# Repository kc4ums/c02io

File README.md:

# C02IO: Raspberry Pi CM5 industrial I/O board (design spec)

**Rev B (2026-11-23): the controller is now a Raspberry Pi Compute Module 5.** Rev A's W65C02S system (CPU, RAM, flash, VIA, UART, address decoding, clock, reset, USB-serial and bus expansion headers) is gone. All the I/O is unchanged except where it meets the logic side, which now runs at 3.3 V. The CM5 adds gigabit Ethernet and a USB-C port for flashing.

Status:
- **Netlist:** `python check_board.py` passes. Every new part was checked against its datasheet (listed at the top of `board.py`).
- **Placement:** `python check_place.py png` passes (no courtyard overlaps, every part inside its isolated area, bridge pads on the right side of each gap). The board grew 10 mm to 230 x 157 mm to fit the 55 x 40 mm module.
- **Schematic:** `python check_sch.py` passes. ERC shows 0 errors and 0 warnings, and KiCad's netlist matches `board.py` (365 nets, 494 parts).
- **PCB:** `mk_pcb.py` builds it. DRC shows 0 errors, with 499 connections still to route.
- **Next:** route it (`python mk_fab.py --route`, see Routing). Lay out the Ethernet and USB pairs carefully first (see Still to do).

This is a small PLC-style controller:
- 16 opto-isolated 24 V digital inputs
- 16 opto-isolated 24 V sourcing outputs, 0.5 A each
- 8 analog inputs and 8 analog outputs, each set to 0-10 V or 4-20 mA with a jumper, isolated as a group
- isolated RS-485 (Modbus RTU)
- gigabit Ethernet, and USB-C for flashing the CM5's eMMC (rpiboot) or a gadget console

## Choices made

| | Choice | Why |
|---|---|---|
| Controller (rev B) | **Raspberry Pi CM5**, on two Amphenol 10164227-1001A1RLF connectors (1.5 mm stack) | Linux, Ethernet, plenty of speed. The footprint is Raspberry Pi's own, from the CM5 IO board's KiCad files (`vendor/cm5io`). Any CM5 variant fits; a Lite one has nowhere to boot from here, so use an eMMC module. |
| Interfaces (rev B) | **Ethernet RJ45, USB-C** | USB-C is a USB 2.0 device port for rpiboot and console. There is no USB host port, HDMI, SD slot or RTC battery. |
| Build | **SMD, assembled by JLCPCB** | You solder the through-hole parts: terminals, headers, the MagJack and the URB converter. |
| Analog | **0-10 V or 4-20 mA, one jumper per channel** | Analog inputs use a 2-pin jumper, analog outputs a 2x3 header with two shunts. |
| Outputs | **Sourcing (high-side), 0.5 A, short-circuit protected** | The standard for PLCs driving relays, valves and lamps. |
| Analog isolation | **Yes, as one group** | The analog section has its own isolated 24 V supply and ground, and talks to the CM5 through digital isolators. The channels share that ground with each other. |
| Layers | **4** | Ground planes under everything, which helps the analog section and the Ethernet pairs. |

## Block diagram

```
 FOUR ISOLATED AREAS: logic (GND), field digital (0V_IO), analog (AGND_ISO), RS-485 (GND_485)

 24V IN --fuse--diode--TVS--+-- TPS54560B buck --> +5V --> CM5 (its 3.3 V output = logic +3V3)
                            +-- URB2424YMD-6WR3 isolated DC-DC --> +24VA, AGND_ISO
                                    +24VA --> 78L05 --> +5VA --> REF3040 (4.096 V)

 CM5 --+-- Ethernet --> MagJack;  USB 2.0 --> USB-C (device)
       |                                                      || FIELD DIGITAL (0V_IO)
       +-- SPI0 <-- 74HC165 x2 <-- pull-ups <-- TLP291-4 x4 <--||---- 16 inputs (LED + opto per input)
       +-- SPI0 --> 74HC595 x2 --> R --> LED of TLP291-4 x4 ---||---> VNI4140K x4 --> 16 outputs, LED each
       |              ^ /OE = watchdog /Q (GPIO5 enable, GPIO4 kick) || STATUS (wire-OR) --> opto --> GPIO22
       |                                                      ||  24V_IO IN --> VNI4140K, 78L05 (+5V_IO); --PTC-->
       |                                                      ||                       sensor supply terminals
       +-- UART0 (RTS = DE) --> CA-IS3082WX -------------------||---- RS-485 A/B (GND_485, from B0505XT)
       +-- SPI1 --> ISO7741 + ISO7720 -------------------------|| ANALOG (AGND_ISO)
                                                              ||-- MCP3208 ADC <-- 8 x (divider, 499R mA jumper, PTC, TVS)
                                                              ||-- DAC7568A --> 8 x (LM324 + NPN, V/I jumper) --> AO
```

Each area has its own ground. Only optocouplers, digital isolators, the isolated DC-DC converters and the isolated RS-485 chip cross between them. The 8 analog channels are isolated from the logic, the field I/O and the power input, but not from each other: they share AGND_ISO.

## CM5 GPIO use

| GPIO | Use |
|---|---|
| 11, 10, 9 | SPI0 SCLK, MOSI, MISO: the shift registers |
| 8 | SPI0 CE0: 74HC595 latch (RCLK). It rises at the end of the transfer, so all 16 outputs change at once. |
| 6 | 74HC165 load (`/PL`): pulse low, then clock the inputs in |
| 21, 20, 19 | SPI1 SCLK, MOSI, MISO, to the analog side through the ISO7741 |
| 18, 16 | SPI1 CE0 = ADC `/CS`, CE2 = DAC `/SYNC` (10k pull-ups) |
| 24 | DAC `/LDAC`: updates all 8 outputs at once |
| 14, 15 | UART0 TX, RX: RS-485 |
| 17 | UART0 RTS: RS-485 driver enable. Use Linux's RS-485 mode, set so the pin is high while sending. A 10k pull-down keeps the driver off during boot, when the bootloader logs on GPIO14/15. |
| 5 | Output enable, pulled low. **The outputs stay off until software sets this.** |
| 4 | Watchdog kick (74HC123: if not toggled for ~100 ms, the outputs drop) |
| 12, 13 | RUN and FAULT LEDs |
| 22 | Output fault in (any VNI4140K over-temperature), through an opto; low = fault |
| 23 | Field power present (24V_IO), through an opto; low = present |
| 2, 3, 7, 25, 26, 27 | Expansion header J11 (2x5): 3V3, 5V, SDA (2), GND, SCL (3), 25, 26, 27, GND, 7. GPIO2/3 have 1.8k pull-ups on the module. |

**One SPI0 transfer does all the digital I/O.** Pulse GPIO6 low, then do one 16-bit transfer on CE0:
- **Out:** the bytes for outputs 16..9 then 8..1, MSB first.
- **In:** the bytes for inputs 8..1 then 16..9, MSB first, low = on. Software inverts them.

CE0 rising at the end of the transfer latches the outputs. Don't use CE0 for a read-only transfer, because it would latch whatever MOSI shifted in.

**Other CM5 pins:**
- **Power and ground:** all 51 ground pins go to GND. 5 V goes to the six VIN pins. GPIO_VREF is tied to the module's own 3.3 V output, which also powers the whole logic side (600 mA max; about 150 mA used).
- **Front-panel controls:** `nRPIBOOT` goes to jumper JP1; fit it before power-up to flash the eMMC over USB-C. `PWR_Button` goes to SW1. The activity LED (`LED_nACT`) is D8.
- **Left open:** PMIC_Enable, EEPROM_nWP, the Wi-Fi/Bluetooth disables, USB_OTG_ID (so it is a device), CC1/CC2, VBAT, fan, SD, PCIe, MIPI, HDMI and USB 3.
- **Power warning:** the CM5 warns about its supply unless it negotiated 5 A over USB-C. Set `PSU_MAX_CURRENT=5000` in its bootloader EEPROM.

## Circuits

**Digital input (x16), IEC 61131-2 type 1/3 style:**
- **Signal path:** terminal → 4.7k (1206) → green LED → opto LED, with 2.2k and 10 nF across the opto LED, then → 0V_IO. An antiparallel 1N4148W protects against reverse voltage.
- **Thresholds:** about 1.7 mA at 11 V reads ON. 5 V stays OFF, because the shunt keeps the opto LED below its threshold. 30 V draws 5.7 mA.
- **Logic side:** the opto transistor pulls the input low against a 22k pull-up to 3.3 V, and a 74HC165 reads it. Software inverts the reading, so 1 = ON.
- **Wiring:** sourcing (PNP) sensors connect between 24V_IO and the input. 0V_IO is the common.

**Digital output (x16):**
- **Signal path:** 74HC595 → 330 Ω → opto LED (about 5 mA from 3.3 V). The opto transistor drives the VNI4140K input from +5V_IO, with a 10k pull-down.
- **Driver:** the VNI4140K is a quad high-side switch: 3.3 V CMOS inputs, 0.6 A per channel in the current datasheet (0.7 A in older ones), current limiting and per-channel thermal shutdown.
- **Indication:** a yellow LED and 4.7k from each output to 0V_IO light when the output is on.
- **Faults:** each VNI4140K has one open-drain STAT pin per channel. All 16 are wire-ORed through one opto to GPIO22. STAT goes low **only on over-temperature** (with IN high), not while the output is current-limiting a short.
- **Supply:** the VNI4140K's exposed slug is **Vcc** (24V_IO), not ground. 24V_IO feeds the four drivers directly (up to 8 A with all outputs on), so **fuse the field supply outside the board**. A reversed field supply is shorted by the SMBJ33A, which must blow that fuse.
- **Start-up and crashes:** the 74HC595s' `/OE` comes from the 74HC123's `/Q`:
  - It stays high (outputs off) until software has written the latches, set GPIO5 and started kicking GPIO4.
  - It goes high again if the kicks stop for about 100 ms. That is about 106 ms at 3.3 V; kick it at least every 25 ms.

**Analog isolation:**
- **Power:** a Mornsun URB2424YMD-6WR3 (9-36 V in, isolated 24 V out, 6 W) makes +24VA on AGND_ISO. A 78L05 makes +5VA for the ADC, DAC and isolators' analog side, and a REF3040 makes the 4.096 V ADC reference.
- **Budget:** 8 outputs at 20 mA from 24 V is about 4 W, plus about 0.5 W for the rest, so the 6 W converter runs at about 75 %.
- **SPI:** an ISO7741 (3 channels to the analog side, 1 back) carries SCLK, MOSI, ADC `/CS` and MISO. An ISO7720 (2 channels) carries DAC `/SYNC` and `/LDAC`. Use the default-high versions, so the chip selects sit inactive while the logic side is unpowered. Side 1 runs at 3.3 V and side 2 at 5 V; the supplies can be set independently. Keep SPI1 at a few MHz: the isolators add about 10 ns each way.

**Analog input (x8):**
- **Signal path:** terminal → PTC (50 mA hold) → SMAJ12A TVS to AGND_ISO → 15k/10k divider (10 V → 4.0 V) → 1k → ADC, with 100 nF and BAV99 clamps to +5VA/AGND_ISO.
- **4-20 mA:** a jumper puts **499 Ω (2010, 0.5 W)** across the input, so 20 mA reads about 9.8 V. Software calibrates it, and a table in software says which channels are mA.
- **ADC:** MCP3208, 12-bit, with a 4.096 V reference (REF3040), so the input range is 0-10.24 V.
- **Mistakes:** 24 V on an input trips the PTC into the TVS.

**Analog output (x8):**
- **DAC:** DAC7568**A**, 12-bit, 8 channels, internal 2.5 V reference, gain 1, so 0-2.5 V. The internal reference is **off at power-up and after a reset**: firmware must enable it. Its outputs drive an LM324 (2 chips, on +24VA), and the op-amp drives an NPN emitter follower (BCX56, SOT-89) from +24VA.
- **Current limit:** a 22 Ω resistor with a sensing transistor limits the output to about 26-29 mA.
- **2x3 jumper:** both shunts left = **0-10 V**: feedback from a 30k/10k divider on the terminal side of the PTC (gain 4), and COM tied to AGND_ISO. Both shunts right = **4-20 mA**: feedback from COM, which returns through a 124 Ω (0.1 %) sense resistor, so 2.5 V gives 20.2 mA.
- **Compensation:** 10k in series with the op-amp's inverting input and 10 nF from its output to that input, plus 10 nF on OUT. These are starting values to check in simulation.
- **Compliance:** about 900 Ω at 20 mA, from the isolated 24 V (only 2.5 V is lost in the sense resistor).
- **Protection:** a PTC and an SMAJ15A TVS at each terminal.
- **Wiring:** in mA mode the load goes between OUT and COM. In V mode, COM is 0 V (AGND_ISO).

**Power:**
- **Input:** 24 V nominal (18-32 V) → 3 A fuse → SS54 reverse diode → SMBJ33A TVS.
- **5 V regulator:** a TPS54560B (4.5-60 V in, 5 A, HSOIC-8) makes +5 V for the CM5 and the RS-485 converter. The values come from TI's 5 V / 5 A design: 400 kHz, B560C catch diode, 10 µH (Bourns SRP1245A), 3 x 47 µF. The CM5 datasheet asks for up to 2.5 A for the module.
- **3.3 V:** from the CM5's own output, so nothing drives a CM5 pin while the module is off.
- **Analog supply:** its own isolated converter (see Analog isolation).
- **Field supply:** 24V_IO is a separate pair of terminals. It can come from the same supply, but isolation only helps if it doesn't.

**RS-485:**
- **Chips:** CA-IS3082WX (isolated transceiver, SOIC-16 wide; logic side 3.3 V, bus side 5 V), powered on the bus side by a B0505XT-1WR3 (SMD) isolated DC-DC converter. The converter needs a 20 mA minimum load, so a 330 Ω resistor (15 mA) sits across its output.
- **Bus side:** a 120 Ω termination jumper (JP3), 680 Ω bias resistors, and an SM712 TVS on A/B.

## Terminals

Pluggable 3.81 mm blocks along the two long edges (headers on the board, plugs in the BOM):

Phoenix MC 1,5/x-G-3.81 headers go up to 16 pins, so the groups are split:

| Ref | Pins | Order |
|---|---|---|
| J2, J3 | 10 each | IN1-IN8 (IN9-IN16), 24V sensor supply (through a 0.5 A PTC), 0V_IO |
| J4 | 10 | OUT1-OUT8, 24V_IO in, 0V_IO in |
| J5 | 10 | OUT9-OUT16, 0V_IO, 0V_IO (load return) |
| J6 | 12 | AI1, AI2, 0V, AI3, AI4, 0V, ... AI7, AI8, 0V |
| J7 | 8 | OUT1, COM1 ... OUT4, COM4 |
| J8 | 9 | OUT5, COM5 ... OUT8, COM8, 0V |
| J1 | 3 | +24 V, 0 V, PE |
| J9 | 3 | A, B, GND_485 |

## Board

- **Size and layers:** **230 x 157 mm**, **4 layers**. Rev A was 230 x 147; the logic band grew 10 mm for the CM5. The 32 field channels sit at the terminals' 3.81 mm pitch, about 45 mm deep with their optos. Each analog channel needs a cell 11 mm (input) or 12.5 mm (output) wide and about 22 mm deep.
- **Bands, top to bottom:** field digital (terminals on the top edge), logic (the CM5 on the right with the Ethernet jack and USB-C on the right edge; 24 V input and power button on the left edge), then analog (terminals on the bottom edge) with RS-485 in the bottom-right corner. The optos, isolators, DC-DC converters and the RS-485 chip straddle the 3 mm gaps between them.
- **Isolation:** four copper areas (logic, field digital, analog, RS-485), each with its own copper on all 4 layers. A ≥3 mm gap separates them, crossed only under the optos, digital isolators, DC-DC converters and the RS-485 chip.
- **B0505XT orientation:** its output 0V (pin 4) is in the same row as the input pins 1 and 2, so its barrier runs between pins 2 and 4, not between the rows. It is turned 270 degrees with the gap between pins 2 and 4. Pin 8 (NC, "isolated from circuitry") ends up on the logic side: leave it unconnected with plane clearance around it.
- **CM5:** nothing is placed under the module, because the 1.5 mm connectors leave no room. Its four M2.5 holes (2.7 mm, unplated) take spacers that suit the stack height.
- **Mounting:** 4 M3 holes, at the left and right edges of the logic band and in the bottom corners. H1 is plated and on PE, with 1 nF 2 kV from PE to logic 0 V. The others are bare. A DIN-rail mount can clip onto the holes.

## Cost notes

- **The CM5** is the biggest item, bought separately and plugged in. Choose an eMMC version.
- **JLCPCB assembly:** most ICs are *extended* parts, each adding a ~$3 loading fee. Check JLCPCB's library for the VNI4140K, CA-IS3082WX, ISO7741/ISO7720, B0505XT-1WR3 and the two Amphenol CM5 connectors. Missing ones can be bought through JLCPCB's global sourcing or soldered by you; the 0.4 mm connectors are best left to JLCPCB.
- **Analog isolation** adds roughly $15-20 per board: the isolated converter (about $8-10) and the two digital isolators.
- **Hand-soldered by you:** the URB2424YMD-6WR3 (through-hole, 25.4 mm square), the TRJG0926HENL MagJack, and the terminal and pin headers.

## Changes in rev B (2026-11-23): CM5 instead of the W65C02S

| Was (rev A) | Now (rev B) | Why |
|---|---|---|
| W65C02S, RAM, flash, W65C22 VIA, TL16C2552 UART, 74HC00/30/138/32 decode, oscillator, DS1813 | Raspberry Pi CM5 | Your request. |
| 74HC541 input buffers, 74HC574 output latches (on the CPU bus) | 74HC165 / 74HC595 shift registers on SPI0 | The CM5 has no parallel bus. |
| `/OE` = NAND(PB0, watchdog OK) | `/OE` = the 74HC123's `/Q`, with `/R` = GPIO5 | The same behaviour without a gate. |
| 5 V logic, 1k opto LED resistors | 3.3 V logic from the CM5, 330 Ω (TLP291 VF 1.2 V, about 5 mA) | CM5 GPIO is 3.3 V. Every logic-side part is rated for it. |
| RS-485 DE = NOT(`/RTSA`) | DE = GPIO17 (UART0 RTS), 10k pull-down | Linux RS-485 mode drives RTS high while sending. |
| USB-serial header, 2x16 bus expansion header | USB-C (device) and a 2x5 GPIO/I2C header | |
| LMR36520, 2 A | TPS54560B, 5 A, with a B560C diode | The CM5 needs up to 2.5 A, plus the RS-485 converter. |
| 230 x 147 mm | 230 x 157 mm | Fits the 55 x 40 mm module. |
| — | Ethernet: TRJG0926HENL MagJack, as on the CM5 IO board | Centre taps to 100 nF, LEDs on nLED3 and nLED2. |

## Changes from the datasheet check (rev A, 2026-11-20)

| Was | Now | Why |
|---|---|---|
| DAC7568**C**, 0-5 V, 249 Ω sense, 10k/10k divider | DAC7568**A**, 0-2.5 V, 124 Ω sense, 30k/10k divider | The C grade gives 0-5 V only with AVDD 5.0-5.5 V; a 78L05 can be 4.75 V. |
| CA-IS3082W | CA-IS3082W**X** | The plain W part was dropped from the datasheet (v1.04/1.05). |
| B0505S-1WR3 (SIP-4) | B0505XT-1WR3 (SMD) + 330 Ω load | Same electrical part in SMD; 20 mA minimum load. |
| URB2424YMD-6WR3 assumed SMD | Through-hole, 25.4 mm | It is a DIP module; added to the hand-soldered list. |
| `RTS` drives DE and `/RE` directly | `/RTS` inverted first | Otherwise the transmitter is on after reset. |
| VNI4140K STATUS (one) | STAT1-4 per chip, all 16 wire-ORed | One per channel; over-temperature only. Slug is Vcc. |
| TLP291 singles for fault / field power | a ninth TLP291-4 (U35), 2 channels spare | The single TLP291 is "not recommended for new design". |
| UART INT to `/IRQ` | through BC847s | INTA/B are active high and 3-state until OUT2. |
| LMR36520 fixed 5 V | adjustable, 100k/24.9k | Rev. C lists no fixed version. Its pin table is the same as the 2020 one. |
| 74HC123 | CD74HC123, 100k/2.2 µF ≈ 100 ms (tW = 0.45 RC) | TI's 74HC123 is the CD74HC123. Kick it at least every 25 ms. |
| reset supervisor not chosen | DS1813R-10 (SOT-23) | Documented pushbutton input, 150 ms stretch. |

## Files

| File | What it is |
|---|---|
| `board.py` | **The design.** Every part, footprint, pin connection, position and rotation, and the isolated areas. Edit this, then regenerate the rest. |
| `check_board.py` | Plain Python. Checks the netlist: pinouts, CM5 pins, shift-register chains, watchdog, isolation, every channel. |
| `check_place.py` | Plain Python + matplotlib. Checks the placement and draws `place.png` (`python check_place.py png`). |
| `mk_fp.py` | Writes the two Mornsun footprints into `c02io.pretty`, from the datasheets' top-view layouts, and copies the CM5 and MagJack footprints from `vendor/cm5io`. |
| `vendor/cm5io/` | Raspberry Pi's CM5 and TRJG0926HENL footprints, unchanged, from the CM5 IO board rev 2 KiCad files. |
| `fpgeom.py` | Reads courtyards and pads from the KiCad libraries; prints the `CRT` table in `board.py`. |
| `mk_pcb.py` | Run with KiCad's Python. Builds `c02io.kicad_pcb` (and the project, rules, `fp-lib-table`): parts, nets, outline, terminal labels, split planes, keep-outs over the gaps. Writes `c02io.dsn` for Freerouting, or imports `c02io.ses` and adds the outer ground pours once routed. |
| `mk_sch.py` | Writes `c02io.kicad_sch` (root) and `sch_*.kicad_sch` (cm5, logic, power, inputs, outputs, analog_in, analog_out, rs485), plus the `c02io` symbol library. Chips are boxes in package pin order with the datasheet pin names. |
| `check_sch.py` | Runs KiCad's ERC and compares the schematic's exported netlist with `board.py`. |
| `mk_fab.py` | Routes (optionally) with Freerouting, runs DRC, and writes the Gerber and drill zip in `fab/`. |

Regenerate after editing `board.py`:

```
python check_board.py
python check_place.py png
python mk_sch.py
python check_sch.py
"C:\Program Files\KiCad\10.0\bin\python.exe" mk_pcb.py
```

## PCB stack-up and rules

- **Layers:** F.Cu, In2.Cu and B.Cu carry tracks. In1.Cu is a plane layer with one ground plane per area: GND (logic), 0V_IO (field), AGND_ISO (analog), GND_485 (RS-485). On In2.Cu the field area is a solid 24V_IO plane, because it carries the outputs' current. In the other areas In2.Cu is also a routing layer: the first route, with both inner layers as planes, left 316 connections unrouted, mostly on the 6502 bus of rev A. Their power pours (+5V, +24VA, +5V_485) are added on In2.Cu after routing, around the tracks, and the power nets are also routed as 0.5 mm tracks.
- **Gaps:** a keep-out over each 3 mm gap stops any track, via or pour from crossing between areas. Only the bridge parts' bodies span them.
- **Net classes:** Default 0.2 mm; Supply 0.5 mm; Output (OUT1-16) 0.8 mm; Field (24V_IO, 0V_IO, 24 V input) 1.5 mm; PE 1.0 mm clearance from everything else. Freerouting necks some tracks down to 0.1 mm for a fraction of a millimetre between fine-pitch pads, so the board minimum is 0.1 mm (JLCPCB 4-layer: 0.09 mm track, 0.3 mm drill). `mk_pcb.py` also corrects the drill of imported vias: KiCad gives every via its net class drill, so 0.6 mm vias on the OUT nets got 0.5 mm holes.
- **TPS54560B:** its thermal pad gets six 0.3 mm vias to GND from `mk_pcb.py`. The library's thermal-via footprint uses 0.2 mm drills, below JLCPCB's standard.

## Still to do

- **Ethernet and USB pairs:** Freerouting knows nothing about differential pairs or impedance.
  - **Ethernet:** 4 pairs at 100 Ω, each P/N matched to 0.15 mm.
  - **USB:** 1 pair at 90 Ω.
  - Over the In1.Cu ground plane on JLCPCB's 4-layer stack, that is roughly 0.15-0.2 mm tracks with a 0.15-0.2 mm gap; check JLCPCB's impedance calculator.
  - Plan: route these 5 pairs by hand, then let Freerouting do the rest. `mk_pcb.py` will need to keep hand-routed tracks across a rebuild.
- **Routing:** see below.
- **Assembly files:** a BOM with LCSC numbers and a pick-and-place file for JLCPCB, once the parts are chosen.

## Routing

Run this from **a normal PowerShell window**, not inside Claude Code, after a reboot with little else open. Freerouting's Java heap is about 2 GB, and on C02COMM a long run inside Claude Code ran the PC low on memory.

```
cd C:\Projects\c02io
python mk_fab.py --route
```

It does these steps in order:
1. `mk_pcb.py` exports `c02io.dsn`.
2. Freerouting (`%LOCALAPPDATA%\freerouting\freerouting.exe`, up to 40 passes, 2 threads) writes `c02io.ses`. Its output also goes to `route_log.txt`.
3. `mk_pcb.py` rebuilds the board, imports the tracks, corrects the via drills, and adds the In2.Cu power pours and a ground pour per area on both outer layers.
4. KiCad's DRC (errors only) goes to `drc.txt`.
5. If the DRC is clean, it writes `fab/c02io_gerbers.zip` (4 copper layers).

`python mk_fab.py --route --passes 3` is a short trial. `python mk_fab.py` alone re-runs the DRC and Gerbers on the routed board.
- **Datasheet details still open:**
  - **CJ78L05 (LCSC C2079):** the pin order (1 OUT, 2 GND, 3 IN) came from a mirror of JSCJ's datasheet; check it against LCSC's copy. The SOT-23 version has a different pinout.
  - **SM712:** read from a third-party copy of Semtech's PDF (2017).
  - **USBLC6-2SC6:** ST's PDF wouldn't download; the pinout is from KiCad's symbol and a second-source drawing.
  - **CA-IS3082WX, VNI4140K:** the newest revisions found were v1.08 (2023) and Rev 5 (2009); the makers' sites weren't reachable.
- **Stock:**
  - **Check:** JLCPCB/LCSC numbers for every SMD part, the Amphenol 10164227-1001A1RLF (x2) and the TRJG0926HENL. If the TRJG can't be had, use another 1:1 gigabit MagJack with LEDs (needs a new footprint).
  - **Choose the PTCs:** 50 mA hold, 30 V+, 1812; 0.5 A for the sensor supply.
- **Output stage stability:** simulate the op-amp, the emitter follower and a long cable with the compensation values in `board.py`.
- **Field supply current:** up to 8 A through J4 pin 9 and the 24V_IO copper with every output on. That is at the terminal's limit: size the copper for it, or split the supply across both DO blocks.
- **Buck heat:** the B560C dissipates about 1.5-2 W at 3-4 A. Give it copper, or change to a synchronous 60 V buck later.

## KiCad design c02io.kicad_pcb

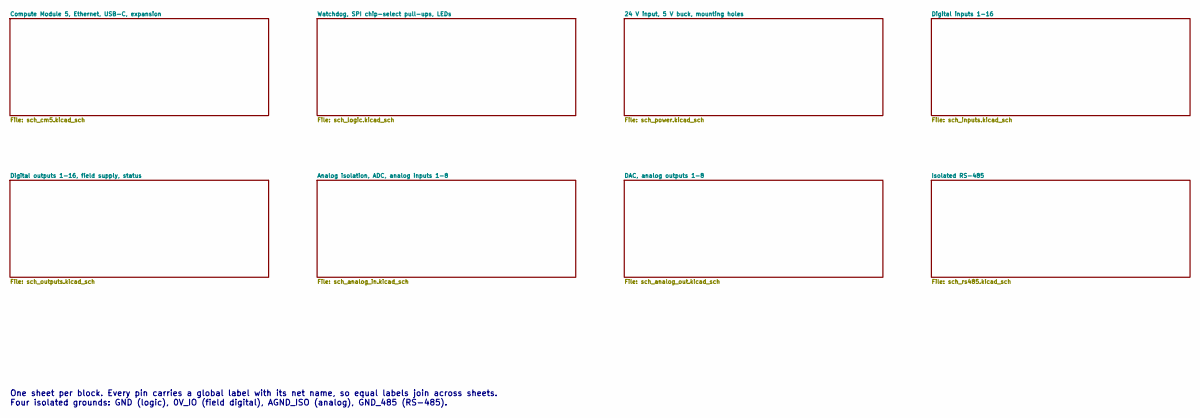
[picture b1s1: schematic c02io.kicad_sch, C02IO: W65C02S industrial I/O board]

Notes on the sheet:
One sheet per block. Every pin carries a global label with its net name, so equal labels join across sheets. Four isolated grounds: GND (logic), 0V_IO (field digital), AGND_ISO (analog), GND_485 (RS-485).

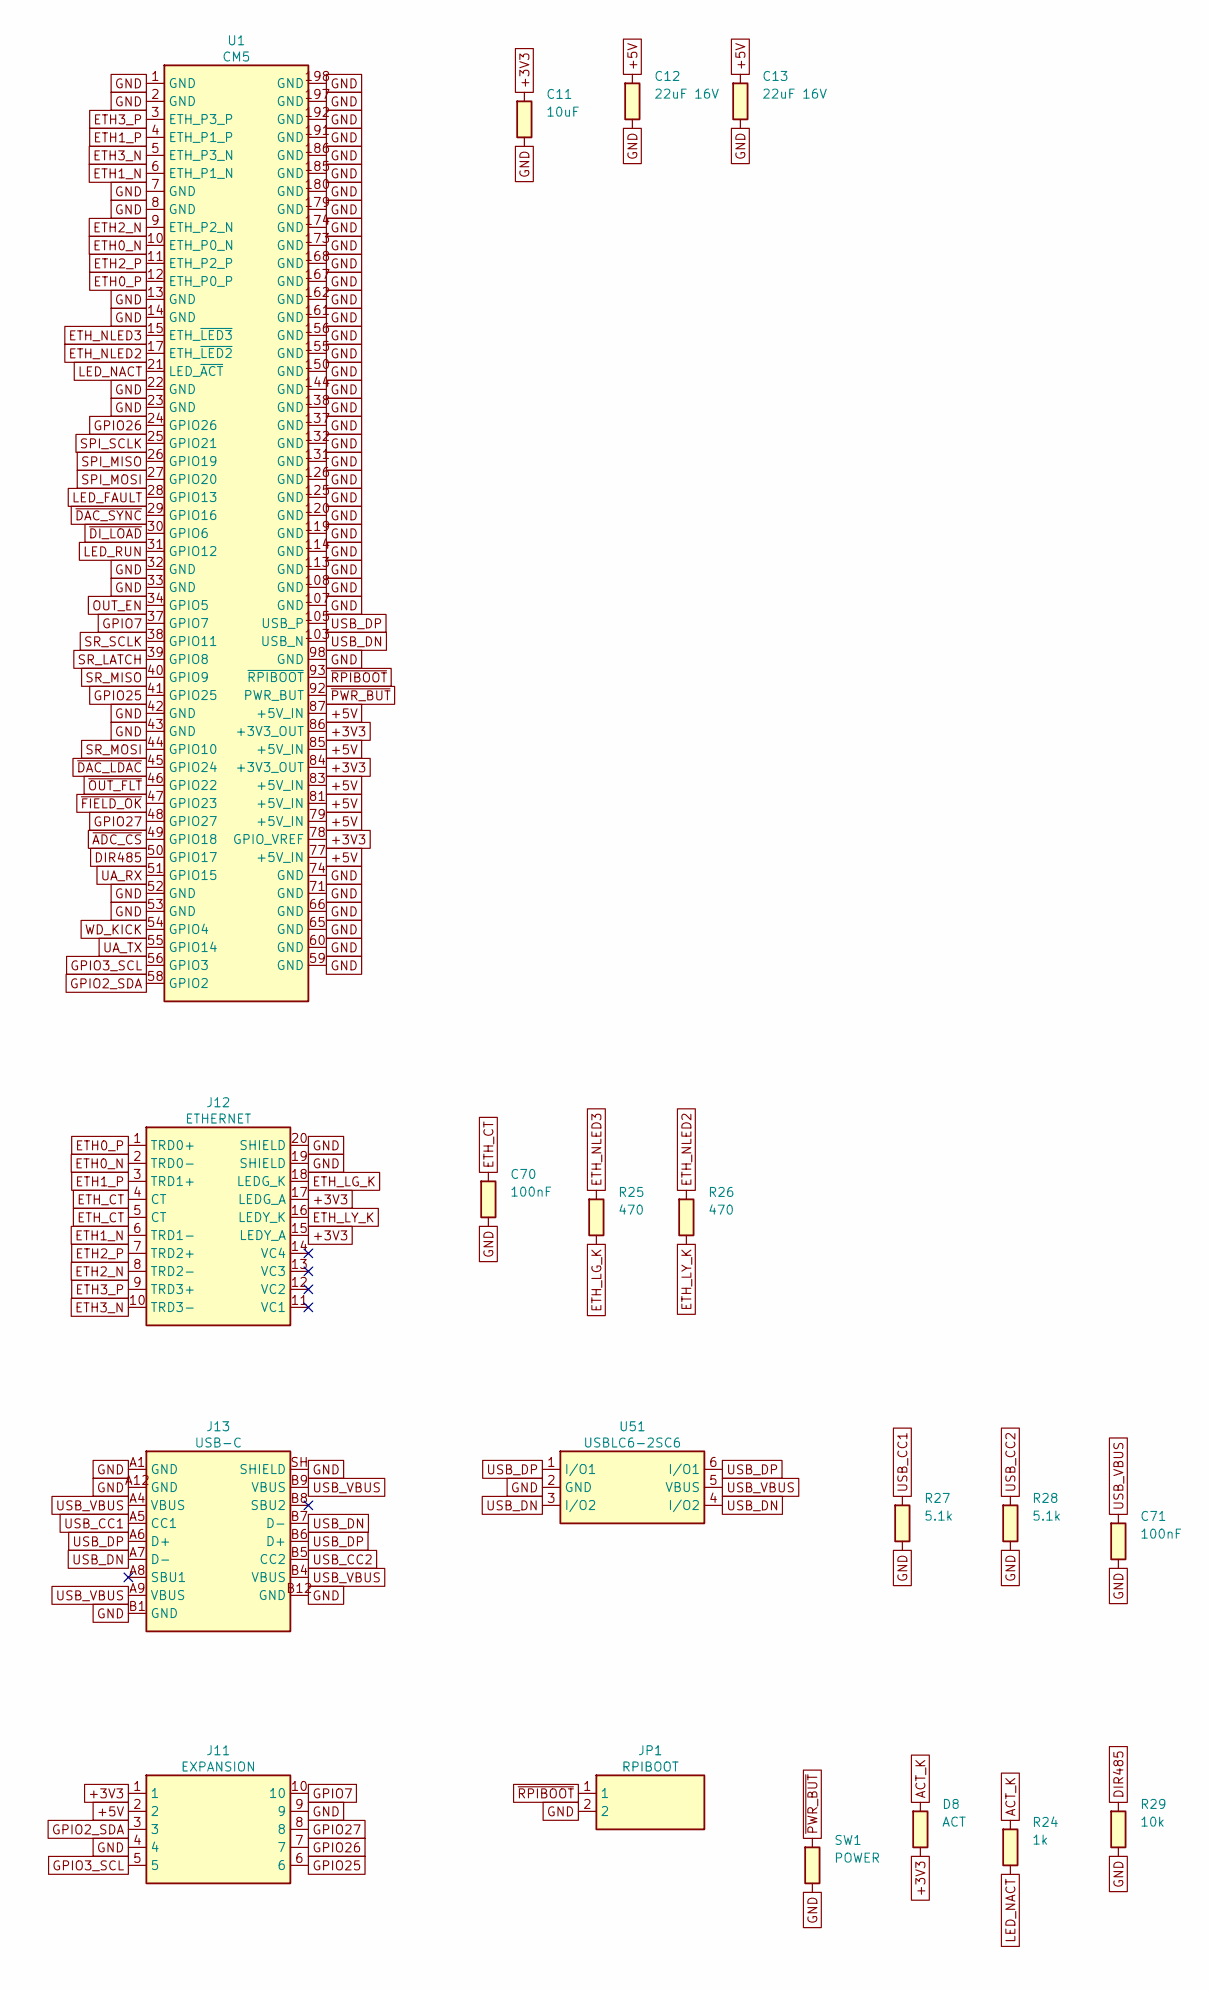
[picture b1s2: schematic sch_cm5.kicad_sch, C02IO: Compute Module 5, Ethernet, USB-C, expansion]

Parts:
C11: 10uF; C_0805_2012Metric
C12, C13: 22uF 16V; C_1210_3225Metric
C70, C71: 100nF; C_0603_1608Metric
D8: ACT; LED_0805_2012Metric; MPN 0805 LED, green
J11: EXPANSION; PinHeader_2x05_P2.54mm_Vertical
J12: ETHERNET; TRJG0926HENL; MPN TRXCOM TRJG0926HENL
J13: USB-C; USB_C_Receptacle_HRO_TYPE-C-31-M-12; MPN Korean Hroparts TYPE-C-31-M-12 (LCSC C1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
JP1: RPIBOOT; PinHeader_1x02_P2.54mm_Vertical
R24: 1k; R_0603_1608Metric
R25, R26: 470; R_0603_1608Metric
R27, R28: 5.1k; R_0603_1608Metric
R29: 10k; R_0603_1608Metric
SW1: POWER; SW_SPST_B3S-1000; MPN Omron B3S-1000
U1: CM5; Raspberry-Pi-5-Compute-Module; MPN Raspberry Pi CM5 (any RAM/eMMC/wireless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
U51: USBLC6-2SC6; SOT-23-6; MPN ST USBLC6-2SC6 (LCSC C7519)

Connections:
+3V3: C11.1, D8.2 (A), J11.1, J12.15 (LEDY_A), J12.17 (LEDG_A), U1.78 (GPIO_VREF), U1.84 (+3V3_OUT), U1.86 (+3V3_OUT); also elsewhere on the board
+5V: C12.1, C13.1, J11.2, U1.77 (+5V_IN), U1.79 (+5V_IN), U1.81 (+5V_IN), U1.83 (+5V_IN), U1.85 (+5V_IN), U1.87 (+5V_IN); also elsewhere on the board
ACT_K: D8.1 (K), R24.1
DIR485: R29.1, U1.50 (GPIO17); also elsewhere on the board
ETH0_N: J12.2 (TRD0-), U1.10 (ETH_P0_N)
ETH0_P: J12.1 (TRD0+), U1.12 (ETH_P0_P)
ETH1_N: J12.6 (TRD1-), U1.6 (ETH_P1_N)
ETH1_P: J12.3 (TRD1+), U1.4 (ETH_P1_P)
ETH2_N: J12.8 (TRD2-), U1.9 (ETH_P2_N)
ETH2_P: J12.7 (TRD2+), U1.11 (ETH_P2_P)
ETH3_N: J12.10 (TRD3-), U1.5 (ETH_P3_N)
ETH3_P: J12.9 (TRD3+), U1.3 (ETH_P3_P)
ETH_CT: C70.1, J12.4 (CT), J12.5 (CT)
ETH_LG_K: J12.18 (LEDG_K), R25.2
ETH_LY_K: J12.16 (LEDY_K), R26.2
ETH_NLED2: R26.1, U1.17 (ETH_~LED2)
ETH_NLED3: R25.1, U1.15 (ETH_~LED3)
GND: C11.2, C12.2, C13.2, C70.2, C71.2, J11.4, J11.9, J12.19 (SHIELD), J12.20 (SHIELD), J13.A1 (GND), J13.A12 (GND), J13.B1 (GND), J13.B12 (GND), J13.SH (SHIELD), JP1.2, R27.2, R28.2, R29.2, SW1.2, U1.1 (GND), U1.2 (GND), U1.7 (GND), U1.8 (GND), U1.13 (GND), U1.14 (GND), U1.22 (GND), U1.23 (GND), U1.32 (GND), U1.33 (GND), U1.42 (GND), U1.43 (GND), U1.52 (GND), U1.53 (GND), U1.59 (GND), U1.60 (GND), U1.65 (GND), U1.66 (GND), U1.71 (GND), U1.74 (GND), U1.98 (GND), U1.107 (GND), U1.108 (GND), U1.113 (GND), U1.114 (GND), U1.119 (GND), U1.120 (GND), U1.125 (GND), U1.126 (GND), U1.131 (GND), U1.132 (GND), U1.137 (GND), U1.138 (GND), U1.144 (GND), U1.150 (GND), U1.155 (GND), U1.156 (GND), U1.161 (GND), U1.162 (GND), U1.167 (GND), U1.168 (GND), U1.173 (GND), U1.174 (GND), U1.179 (GND), U1.180 (GND), U1.185 (GND), U1.186 (GND), U1.191 (GND), U1.192 (GND), U1.197 (GND), U1.198 (GND), U51.2 (GND); also elsewhere on the board
GPIO2_SDA: J11.3, U1.58 (GPIO2)
GPIO3_SCL: J11.5, U1.56 (GPIO3)
GPIO7: J11.10, U1.37 (GPIO7)
GPIO25: J11.6, U1.41 (GPIO25)
GPIO26: J11.7, U1.24 (GPIO26)
GPIO27: J11.8, U1.48 (GPIO27)
LED_FAULT: U1.28 (GPIO13); also elsewhere on the board
LED_NACT: R24.2, U1.21 (LED_~ACT)
LED_RUN: U1.31 (GPIO12); also elsewhere on the board
OUT_EN: U1.34 (GPIO5); also elsewhere on the board
SPI_MISO: U1.26 (GPIO19); also elsewhere on the board
SPI_MOSI: U1.27 (GPIO20); also elsewhere on the board
SPI_SCLK: U1.25 (GPIO21); also elsewhere on the board
SR_LATCH: U1.39 (GPIO8); also elsewhere on the board
SR_MISO: U1.40 (GPIO9); also elsewhere on the board
SR_MOSI: U1.44 (GPIO10); also elsewhere on the board
SR_SCLK: U1.38 (GPIO11); also elsewhere on the board
UA_RX: U1.51 (GPIO15); also elsewhere on the board
UA_TX: U1.55 (GPIO14); also elsewhere on the board
USB_CC1: J13.A5 (CC1), R27.1
USB_CC2: J13.B5 (CC2), R28.1
USB_DN: J13.A7 (D-), J13.B7 (D-), U1.103 (USB_N), U51.3 (I/O2), U51.4 (I/O2)
USB_DP: J13.A6 (D+), J13.B6 (D+), U1.105 (USB_P), U51.1 (I/O1), U51.6 (I/O1)
USB_VBUS: C71.1, J13.A4 (VBUS), J13.A9 (VBUS), J13.B4 (VBUS), J13.B9 (VBUS), U51.5 (VBUS)
WD_KICK: U1.54 (GPIO4); also elsewhere on the board
~ADC_CS: U1.49 (GPIO18); also elsewhere on the board
~DAC_LDAC: U1.45 (GPIO24); also elsewhere on the board
~DAC_SYNC: U1.29 (GPIO16); also elsewhere on the board
~DI_LOAD: U1.30 (GPIO6); also elsewhere on the board
~FIELD_OK: U1.47 (GPIO23); also elsewhere on the board
~OUT_FLT: U1.46 (GPIO22); also elsewhere on the board
~PWR_BUT: SW1.1, U1.92 (PWR_BUT)
~RPIBOOT: JP1.1, U1.93 (~RPIBOOT)

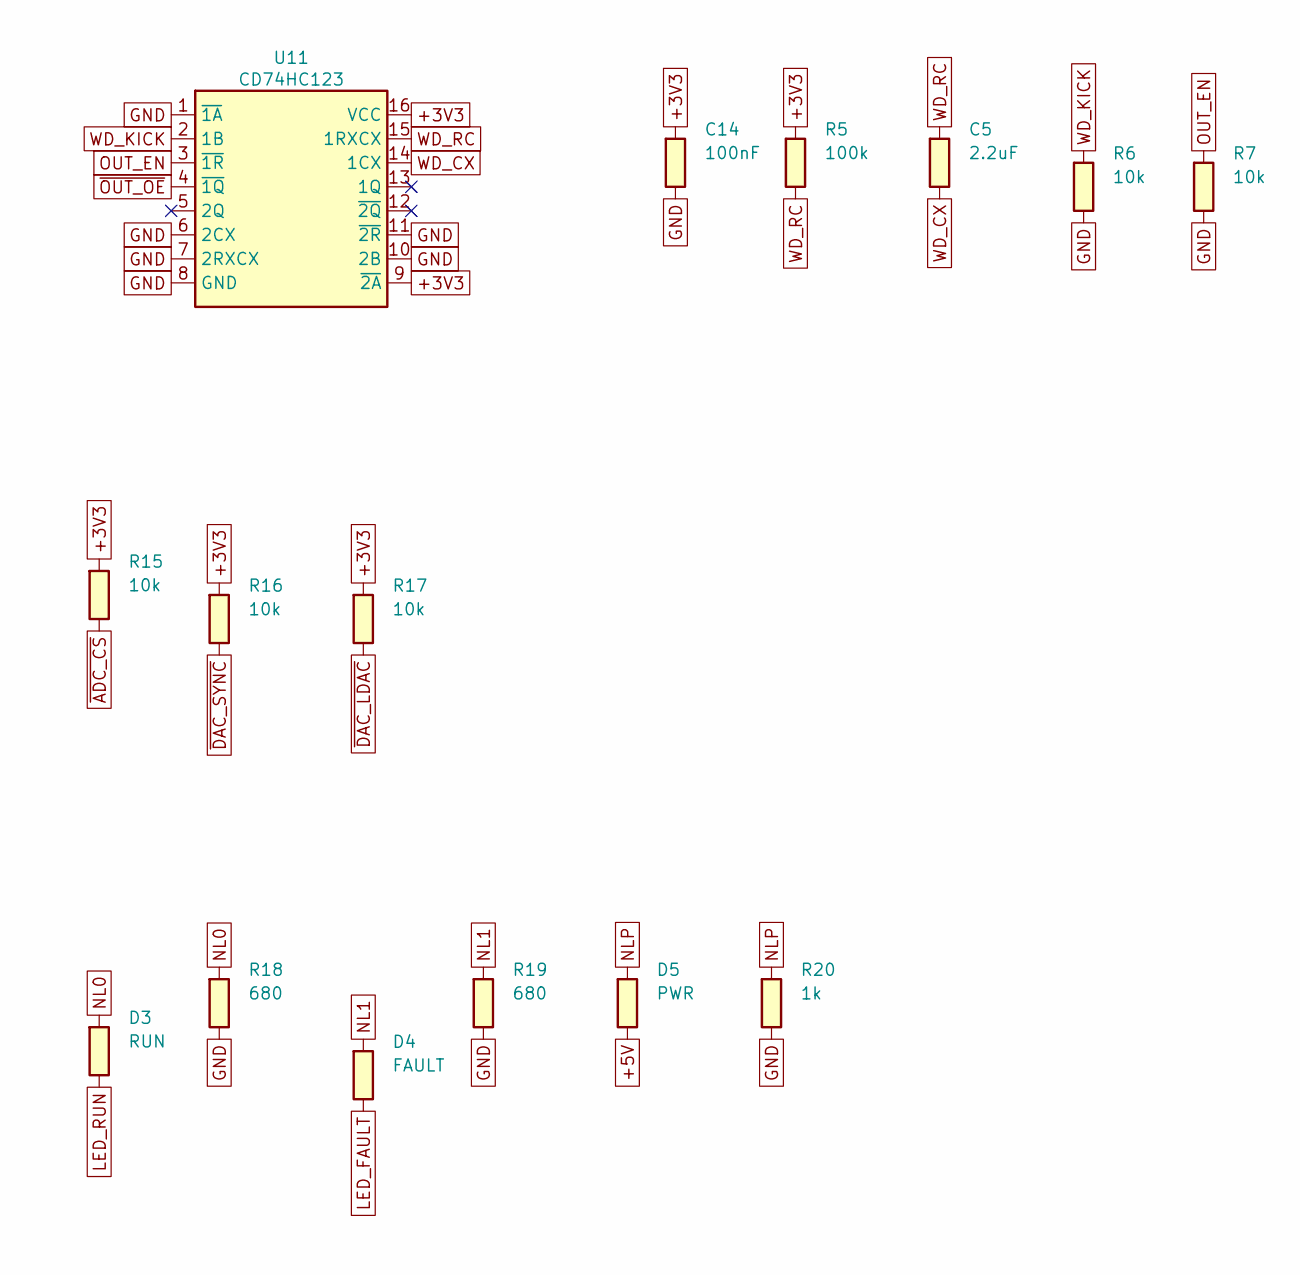
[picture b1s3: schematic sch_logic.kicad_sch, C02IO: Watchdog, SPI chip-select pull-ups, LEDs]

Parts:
C5: 2.2uF; C_1206_3216Metric
C14: 100nF; C_0603_1608Metric
D3: RUN; LED_0805_2012Metric; MPN 0805 LED, green
D4: FAULT; LED_0805_2012Metric; MPN 0805 LED, red
D5: PWR; LED_0805_2012Metric; MPN 0805 LED, green
R5: 100k; R_0603_1608Metric
R6, R7, R15, R16, R17: 10k; R_0603_1608Metric
R18, R19: 680; R_0603_1608Metric
R20: 1k; R_0603_1608Metric
U11: CD74HC123; SOIC-16_3.9x9.9mm_P1.27mm; MPN TI CD74HC123M96

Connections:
+3V3: C14.1, R5.1, R15.1, R16.1, R17.1, U11.9 (~2A), U11.16 (VCC); also elsewhere on the board
+5V: D5.2 (A); also elsewhere on the board
GND: C14.2, R6.2, R7.2, R18.2, R19.2, R20.2, U11.1 (~1A), U11.6 (2CX), U11.7 (2RXCX), U11.8 (GND), U11.10 (2B), U11.11 (~2R); also elsewhere on the board
LED_FAULT: D4.2 (A); also elsewhere on the board
LED_RUN: D3.2 (A); also elsewhere on the board
NL0: D3.1 (K), R18.1
NL1: D4.1 (K), R19.1
NLP: D5.1 (K), R20.1
OUT_EN: R7.1, U11.3 (~1R); also elsewhere on the board
WD_CX: C5.2, U11.14 (1CX)
WD_KICK: R6.1, U11.2 (1B); also elsewhere on the board
WD_RC: C5.1, R5.2, U11.15 (1RXCX)
~ADC_CS: R15.2; also elsewhere on the board
~DAC_LDAC: R17.2; also elsewhere on the board
~DAC_SYNC: R16.2; also elsewhere on the board
~OUT_OE: U11.4 (~1Q); also elsewhere on the board

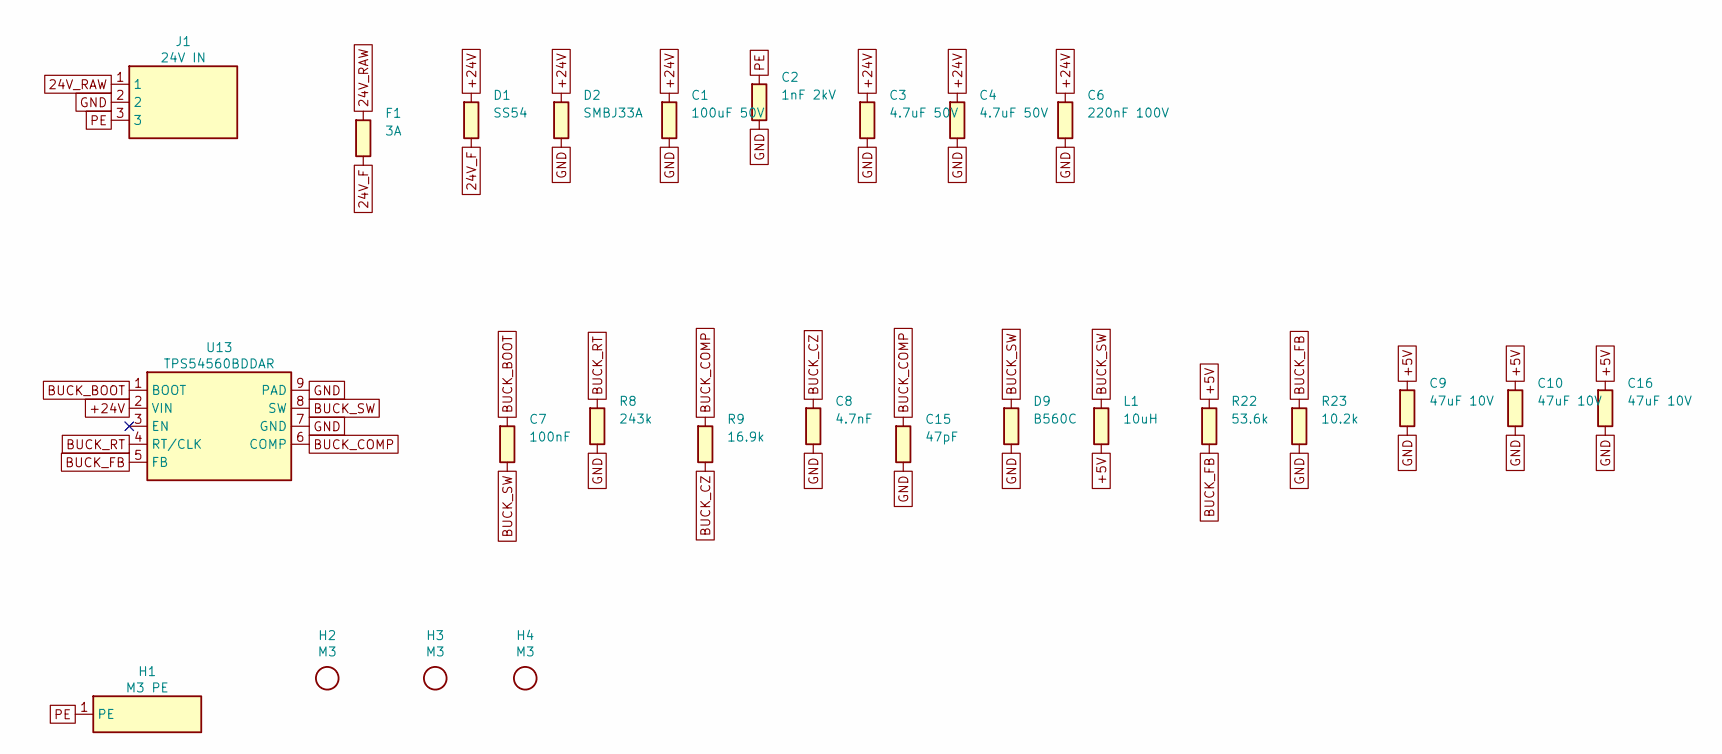
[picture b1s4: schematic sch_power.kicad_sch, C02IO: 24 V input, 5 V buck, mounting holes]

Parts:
C1: 100uF 50V; CP_Elec_10x10.5
C2: 1nF 2kV; C_1808_4520Metric
C3, C4: 4.7uF 50V; C_1210_3225Metric
C6: 220nF 100V; C_0805_2012Metric
C7: 100nF; C_0603_1608Metric
C8: 4.7nF; C_0603_1608Metric
C9, C10, C16: 47uF 10V; C_1210_3225Metric
C15: 47pF; C_0603_1608Metric
D1: SS54; D_SMB
D2: SMBJ33A; D_SMB
D9: B560C; D_SMC
F1: 3A; Fuse_1206_3216Metric
H1: M3 PE; MountingHole_3.2mm_M3_Pad
H2, H3, H4: M3; MountingHole_3.2mm_M3
J1: 24V IN; PhoenixContact_MC_1,5_3-G-3.81_1x03_P3.81mm_Horizontal
L1: 10uH; L_Bourns_SRP1245A; MPN Bourns SRP1245A-100M
R8: 243k; R_0603_1608Metric
R9: 16.9k; R_0603_1608Metric
R22: 53.6k; R_0603_1608Metric
R23: 10.2k; R_0603_1608Metric
U13: TPS54560BDDAR; HSOP-8-1EP_3.9x4.9mm_P1.27mm_EP2.41x3.1mm; MPN TI TPS54560BDDAR (LCSC C1850354)

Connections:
24V_F: D1.2 (A), F1.2
24V_RAW: F1.1, J1.1
+5V: C9.1, C10.1, C16.1, L1.2, R22.1; also elsewhere on the board
+24V: C1.1 (+), C3.1, C4.1, C6.1, D1.1 (K), D2.1 (K), U13.2 (VIN); also elsewhere on the board
BUCK_BOOT: C7.1, U13.1 (BOOT)
BUCK_COMP: C15.1, R9.1, U13.6 (COMP)
BUCK_CZ: C8.1, R9.2
BUCK_FB: R22.2, R23.1, U13.5 (FB)
BUCK_RT: R8.1, U13.4 (RT/CLK)
BUCK_SW: C7.2, D9.1 (K), L1.1, U13.8 (SW)
GND: C1.2, C2.2, C3.2, C4.2, C6.2, C8.2, C9.2, C10.2, C15.2, C16.2, D2.2 (A), D9.2 (A), J1.2, R8.2, R23.2, U13.7 (GND), U13.9 (PAD); also elsewhere on the board
PE: C2.1, H1.1, J1.3
